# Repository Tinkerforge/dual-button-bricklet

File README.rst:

Dual Button Bricklet
====================

This repository contains the firmware source code and the hardware design
files. The documentation generator configs can be found at
https://github.com/Tinkerforge/generators

Repository Content
------------------

software/:
 * examples/: Examples for all supported languages
 * build/: Compiled files
 * src/: Source code of firmware
 * Makefile: Makefile to build project

hardware/:
 * Contains KiCad project files and additionally schematics as PDF

datasheets/:
 * Contains datasheets for sensors and complex ICs that are used

Hardware
--------

The hardware is designed with the open source EDA Suite KiCad
(http://www.kicad.org). Before you are able to open the files,
you have to install the Tinkerforge kicad-libraries
(https://github.com/Tinkerforge/kicad-libraries). You can either clone
them directly in hardware/ or clone them in a separate folder and
symlink them into hardware/
(ln -s kicad_path/kicad-libraries project_path/hardware). After that you
can open the .pro file in hardware/ with KiCad and from there view and
modify the schematics and the PCB layout.

Software
--------

If you want to do your own Brick/Bricklet firmware development we highly
recommend that you use our build environment setup script and read the
tutorial (https://www.tinkerforge.com/en/doc/Tutorials/Tutorial_Build_Environment/Tutorial.html).

To compile the C code we recommend you to install the newest GNU Arm Embedded
Toolchain (https://launchpad.net/gcc-arm-embedded/+download).
You also need to install bricklib (https://github.com/Tinkerforge/bricklib)
and brickletlib (https://github.com/Tinkerforge/brickletlib).

You can either clone it directly in software/src/ or clone it in a
separate folder and symlink it into software/src/
(ln -s bricklib_path/bricklib project_path/software/src/ and
ln -s brickletlib_path/brickletlib project_path/software/src/).
Finally make sure to have CMake installed
(http://www.cmake.org/cmake/resources/software.html).

After that you can build the firmware by invoking make in software/.
The firmware (.bin) can then be found in software/build/ and uploaded
with brickv (click button "Flashing" on start screen).

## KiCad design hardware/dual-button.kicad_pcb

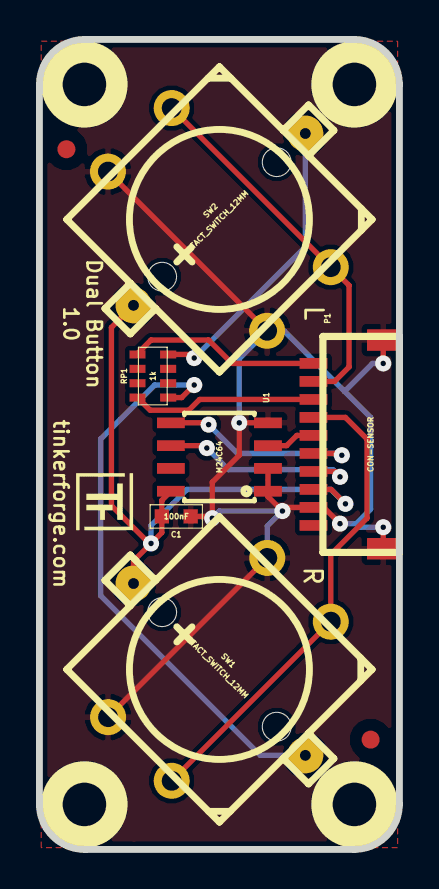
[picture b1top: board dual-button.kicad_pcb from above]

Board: 2 copper layers, 20.0 x 45.0 mm, 15 parts (0 on the bottom side), 11 nets.

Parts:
C1: 100nF; 0603
Fiducial_Mark: VAL**; Fiducial_Mark
Fiducial_Mark#2: VAL**; Fiducial_Mark
P1: CON-SENSOR
RP1: 1k; 4X0603
Ref**: Val**; Logo_31x31
SW1, SW2: TACT_SWITCH_12MM; TACT_SWITCH_12mm
U1: M24C64; SOIC8
U2, U3, U4, U5: DRILL; DRILL_NP
VAL: WEEE_7mm
VAL#2: CE_5mm

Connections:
D1: P1.8, RP1.1
D2: P1.10, RP1.4
GND: C1.1, P1.2, P1.EP, SW1.3, SW2.3, U1.1, U1.2, U1.4
unnamed: RP1.5, SW2.2
unnamed: RP1.8, SW1.2
unnamed: P1.6, U1.3
SCL: P1.4, U1.6
SDA: P1.5, U1.5
SW1: P1.7, SW1.4
SW2: P1.9, SW2.4
VCC: C1.2, P1.3, SW1.1, SW2.1, U1.8

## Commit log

2013-07-23 Initial commit for Dual Button Bricklet
2013-07-23 Add prototype disclaimer to README.rst
2013-08-21 windows: Don't trigger a build in generate_makefile.bat
    Also use normal make instead of a special named one.
2013-08-26 Rename 1 -> r, 2 -> l
2013-09-11 Add examples for Dual Button Bricklet
2013-09-20 c: Avoid unused parameter warnings
2013-10-15 hardware files checkin
2013-10-15 add licence file
2013-10-17 Change default LED state to auto-toggle-off
2013-10-18 Add SetSelectedLEDState API for Dual Button Bricklet
2013-10-18 Fix name to fit naming standard
2014-01-06 php: Fix indentation
2014-01-10 Add Perl examples
2014-01-14 perl: Fix warning about unsharing the $db variable
2014-01-15 php: Use const for constant values
2014-01-20 Fix selected_led_state bug
2014-01-20 Fix mixup in firmware/hardware version
2014-01-21 Fix left/right button permutation
2014-02-07 Add Mathematica examples
2014-02-10 perl: fixed namespace
2014-02-11 javascript: adding examples
2014-02-11 javascript: error message fixed
2014-02-11 javascript: short examples
2014-02-18 javascript: examples fixed
2014-02-19 javascript: add comment
2014-02-19 javascript: add html examples
2014-02-20 javascript: delete Tinkerforge.js
2014-02-24 javascript: port 4280, startExample()
2014-02-28 javascript: Break long lines and cleanup whitespace
2014-03-05 Add LabVIEW example
2014-03-06 labview: Add example in LV2010 format
2014-03-25 matlab: add examples
2014-04-02 java: Unify constants style
2014-04-02 perl: Unify print style
2014-04-17 matlab: Adapt examples to new callback style
2014-04-17 matlab: Add parentheses to make pygments happy
2014-07-15 java: Replace System.console() usage with an Eclipse compatible pattern
2014-12-02 Use ReadLine instead of ReadKey for C# example
2015-02-13 vbnet: Use ReadLine instead of ReadKey
    Because ReadKey doesn't work with a pipe as stdin on the RED Brick.
2015-03-02 windows: Stop cmake from searching for mingw32-make.exe
    Using MinGW Makefiles as generator makes cmake search for mingw32-make.exe
    which might not be installed because GnuWin32's make.exe is used instead.
2015-04-09 c: Whitespace
2015-06-18 Break long line in VB.NET example
2015-06-24 javascript: Clean up output creation
2015-06-29 octave: Handle short difference between Octave 3.6 and 3.8
    In Octave 3.6 a short is not automatically handled as a number.
2015-07-23 Make JavaScript browser example textarea readonly
2015-07-27 Cleanup C/C++, C#, Java and Python examples
2015-07-29 Reformat changelog
2015-08-07 Use full device class name in Python example
2015-08-12 Fix minor warnings in C/C++ examples
2015-08-19 Cleanup Perl example
2015-09-09 Duplicate cmake call to fix bug during cmake creation
2015-09-30 Generator based example cleanup
2015-11-12 matlab: Fix callback handling for R2014a
    http://undocumentedmatlab.com/blog/matlab-callbacks-for-java-events-in-r2014a
2015-11-25 Include date and commit into changelog
2015-11-30 vbnet: Unbreak long line for now
2016-05-18 c: Add missing device destroy call
2016-07-01 Make the change UID comment more explicit
2017-04-13 csharp: Adapt example
2017-05-12 python: Use correct class anme
2017-05-22 add button diameter marking
2017-06-02 octave: Use javaObject instead of deprecated java_new
2017-11-30 Update examples from generator
2017-12-07 mathematica: Also generate .nb files
2018-02-19 javascript: Close div tag correctly
2018-02-20 Cleanup KiCad libraries config
    Ensure LibDir=kicad-libraries and LibName1=tinkerforge.
    Remove special library.
2018-05-11 Rename files
2018-05-24 perl: Use strict in examples
2018-05-25 labview: Fix wrong comment
2018-05-28 examples: Unify constant printing style
2018-07-11 Add Makefile with docker support
2018-07-11 Update directory structure and build instructions
2018-07-11 Remove obsolete generate_makefile scripts
2018-11-06 Add rust examples
2018-11-07 rust: Accept host names for ip connection, fix naming inconsistencies
2018-11-07 rust: Rename callback receivers.
2018-12-14 Add go examples.
2018-12-18 go: Change import path.
2018-12-18 go: Change import path again.
2018-12-20 rust: Reformat examples.
2019-01-24 mqtt: Add examples.
2019-01-24 mqtt: Fix example header.
2019-01-24 mqtt: Remove executable bit in example permissions.
2019-01-24 go: Minor example fixes.
2019-08-22 c: Adapt to bindings changes
2020-01-13 examples: Use python3 input instead of python2 raw_input.
2021-10-25 Update KiCad link
    https://www.kicad.org/blog/2021/10/Avoid-links-to-former-kicad-domain/
2022-07-06 Add license files.

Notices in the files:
hardware/dual-button.kicad_pcb:
Licensed under CERN OHL v.1.1
Copyright (©) 2013, B.Nordmeyer
Copyright Tinkerforge GmbH 2013.
This documentation describes Open Hardware and is licensed under the
CERN OHL v. 1.1.
